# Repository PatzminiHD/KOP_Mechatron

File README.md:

# Mechatron

The git-repository for our KOP Project

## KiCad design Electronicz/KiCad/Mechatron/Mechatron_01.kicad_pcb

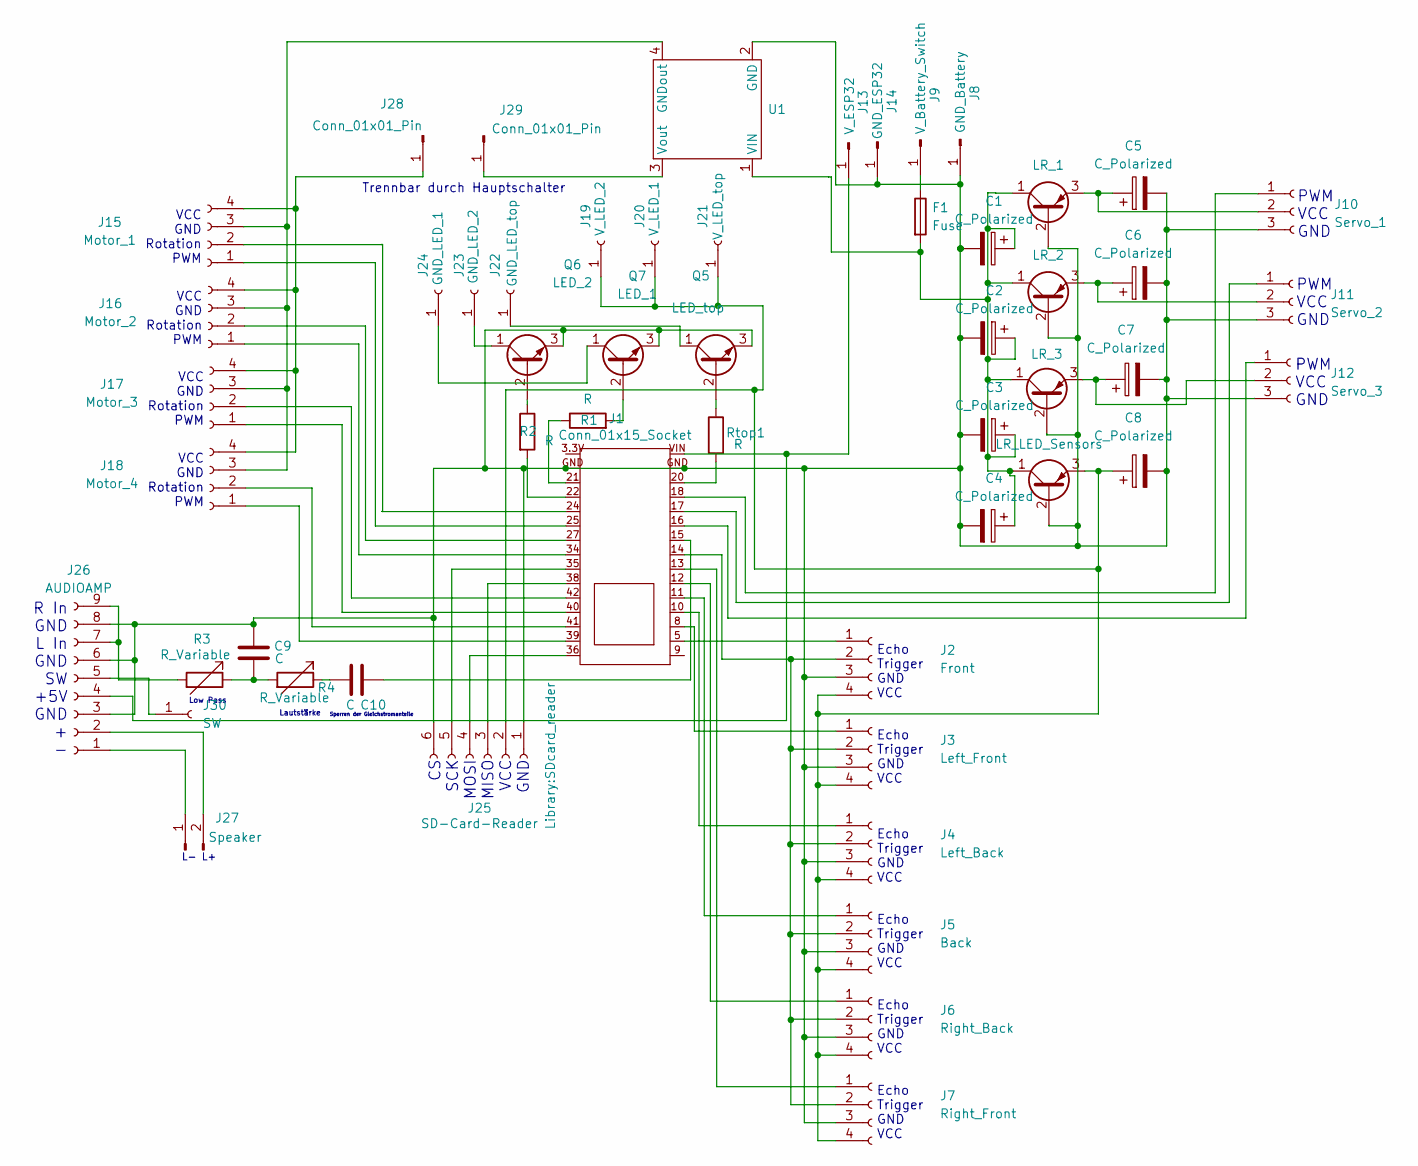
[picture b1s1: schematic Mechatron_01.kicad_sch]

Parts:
C1, C2, C3, C4, C5, C6, C7, C8: C_Polarized; C_Disc_D4.3mm_W1.9mm_P5.00mm
C9, C10: C; C_Disc_D3.0mm_W1.6mm_P2.50mm
F1: Fuse; Fuseholder_Clip-5x20mm_Eaton_1A5601-01_Inline_P20.80x6.76mm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
J1: Conn_01x15_Socket; ESP32
J2: Front; PinSocket_1x04_P2.54mm_Vertical
J3: Left_Front; PinSocket_1x04_P2.54mm_Vertical
J4: Left_Back; PinSocket_1x04_P2.54mm_Vertical
J5: Back; PinSocket_1x04_P2.54mm_Vertical
J6: Right_Back; PinSocket_1x04_P2.54mm_Vertical
J7: Right_Front; PinSocket_1x04_P2.54mm_Vertical
J8: GND_Battery; PinHeader_1x01_P2.54mm_Vertical
J9: V_Battery_Switch; PinHeader_1x01_P2.54mm_Vertical
J10: Servo_1; PinSocket_1x03_P2.54mm_Vertical
J11: Servo_2; PinSocket_1x03_P2.54mm_Vertical
J12: Servo_3; PinSocket_1x03_P2.54mm_Vertical
J13: V_ESP32; PinHeader_1x01_P2.54mm_Vertical
J14: GND_ESP32; PinHeader_1x01_P2.54mm_Vertical
J15: Motor_1; PinSocket_1x04_P2.54mm_Vertical
J16: Motor_2; PinSocket_1x04_P2.54mm_Vertical
J17: Motor_3; PinSocket_1x04_P2.54mm_Vertical
J18: Motor_4; PinSocket_1x04_P2.54mm_Vertical
J19: V_LED_2; PinSocket_1x01_P2.54mm_Vertical
J20: V_LED_1; PinSocket_1x01_P2.54mm_Vertical
J21: V_LED_top; PinSocket_1x01_P2.54mm_Vertical
J22: GND_LED_top; PinSocket_1x01_P2.54mm_Vertical
J23: GND_LED_2; PinSocket_1x01_P2.54mm_Vertical
J24: GND_LED_1; PinSocket_1x01_P2.54mm_Vertical
J25: SD-Card-Reader; SDcard_reader
J26: AUDIOAMP; PinSocket_1x09_P2.00mm_Vertical
J27: Speaker; PinHeader_1x02_P2.54mm_Vertical
J28, J29: Conn_01x01_Pin; PinHeader_1x01_P2.54mm_Vertical
J30: SW; PinSocket_1x01_P2.00mm_Vertical
Q1: LR_LED_Sensors; TO-126-3_Vertical
Q2: LR_3; TO-126-3_Vertical
Q3: LR_2; TO-126-3_Vertical
Q4: LR_1; TO-126-3_Vertical
Q5: LED_top; TO-92_Inline
Q6: LED_2; TO-92_Inline
Q7: LED_1; TO-92_Inline
R1, R2: R; R_Axial_DIN0207_L6.3mm_D2.5mm_P10.16mm_Horizontal
R3: R_Variable; Potentiometer_Bourns_3386C_Horizontal
R4: R_Variable; R_Axial_DIN0207_L6.3mm_D2.5mm_P10.16mm_Horizontal
Rtop1: R; R_Axial_DIN0207_L6.3mm_D2.5mm_P10.16mm_Horizontal
U1: Spannungsregler

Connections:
unnamed: C9.2, R3.1, R4.2
unnamed: C10.1, J1.15
unnamed: C10.2, R4.1
unnamed: J1.20, Rtop1.2
unnamed: J1.21, R1.1
unnamed: J1.22, R2.2
unnamed: J1.5, J2.1
unnamed: J1.14, J2.2, J3.2, J4.2, J5.2, J6.2, J7.2
unnamed: J1.8, J3.1
unnamed: J1.10, J4.1
unnamed: J1.11, J5.1
unnamed: J1.12, J6.1
unnamed: J1.13, J7.1
unnamed: F1.1, J9.1
unnamed: J1.18, J10.1
unnamed: C5.1, J10.2, Q4.3 (E)
unnamed: C1.2, C2.2, C3.2, C4.2, C5.2, C6.2, C7.2, C8.2, C9.1, J1.GND, J2.3, J3.3, J4.3, J5.3, J6.3, J7.3, J8.1, J10.3, J11.3, J12.3, J14.1, J25.1, J25.6, J26.3, J26.6, J26.8, Q1.2 (B), Q2.2 (B), Q3.2 (B), Q4.2 (B), Q5.3 (E), Q6.3 (E), Q7.3 (E), U1.2 (GND)
unnamed: J1.17, J11.1
unnamed: C6.1, J11.2, Q3.3 (E)
unnamed: J1.16, J12.1
unnamed: C7.1, J12.2, Q2.3 (E)
unnamed: J1.VIN, J13.1, J26.4
unnamed: J1.25, J15.1
unnamed: J1.24, J15.2
unnamed: J15.3, J16.3, J17.3, J18.3, U1.4 (GNDout)
unnamed: J15.4, J16.4, J17.4, J18.4, J28.1
unnamed: J1.34, J16.1
unnamed: J1.27, J16.2
unnamed: J1.40, J17.1
unnamed: J1.42, J17.2
unnamed: J1.39, J18.1
unnamed: J1.41, J18.2
unnamed: C8.1, J2.4, J3.4, J4.4, J5.4, J6.4, J7.4, J19.1, J20.1, J21.1, J25.2, Q1.3 (E)
unnamed: J22.1, Q5.1 (C)
unnamed: J23.1, Q6.1 (C)
unnamed: J24.1, Q7.1 (C)
unnamed: J1.38, J25.3
unnamed: J1.36, J25.4
unnamed: J1.35, J25.5
unnamed: J26.1, J27.1
unnamed: J26.2, J27.2
unnamed: J26.5, J30.1
unnamed: J26.7, J26.9, R3.2
unnamed: J29.1, U1.3 (Vout)
unnamed: C1.1, C2.1, C3.1, C4.1, F1.2, Q1.1 (C), Q2.1 (C), Q3.1 (C), Q4.1 (C), U1.1 (VIN)
unnamed: Q5.2 (B), Rtop1.1
unnamed: Q6.2 (B), R2.1
unnamed: Q7.2 (B), R1.2

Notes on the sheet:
Trennbar durch Hauptschalter
Echo Trigger GND VCC
PWM VCC GND
Low Pass
Lautstärke
VCC GND Rotation PWM
CS SCK MOSI MISO VCC GND
Sperren der Gleichstromanteile
R In GND L In GND SW +5V GND + -
L- L+

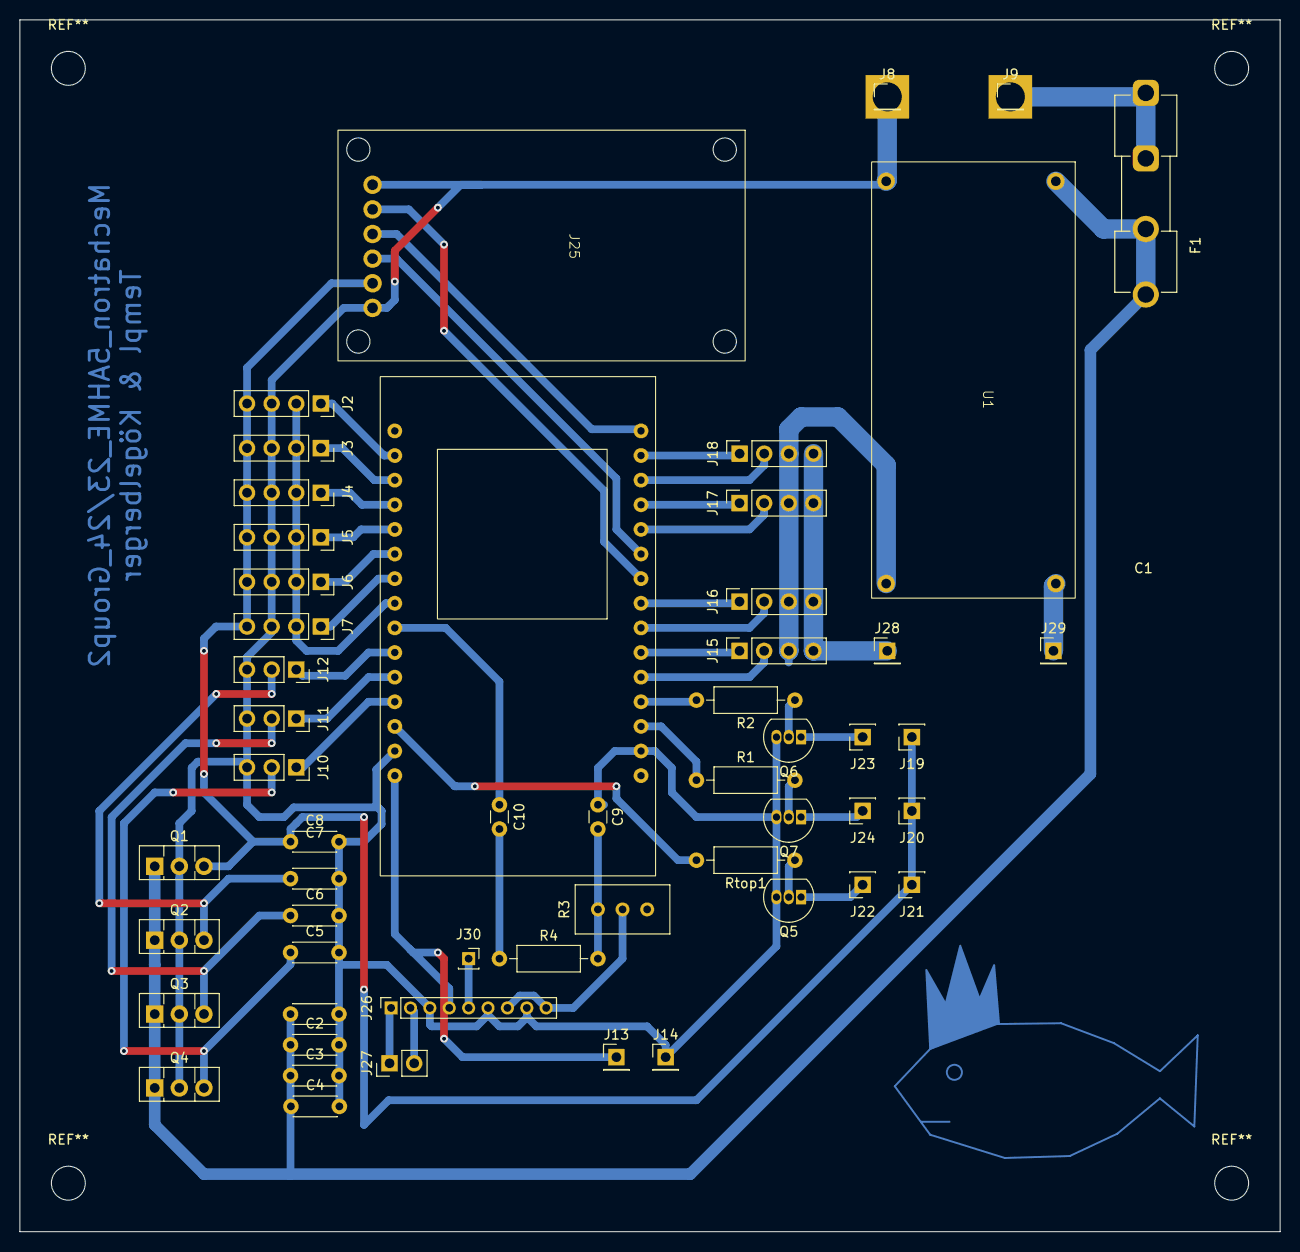
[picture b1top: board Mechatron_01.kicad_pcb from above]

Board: 2 copper layers, 130.0 x 125.0 mm, 54 parts (0 on the bottom side), 48 nets.

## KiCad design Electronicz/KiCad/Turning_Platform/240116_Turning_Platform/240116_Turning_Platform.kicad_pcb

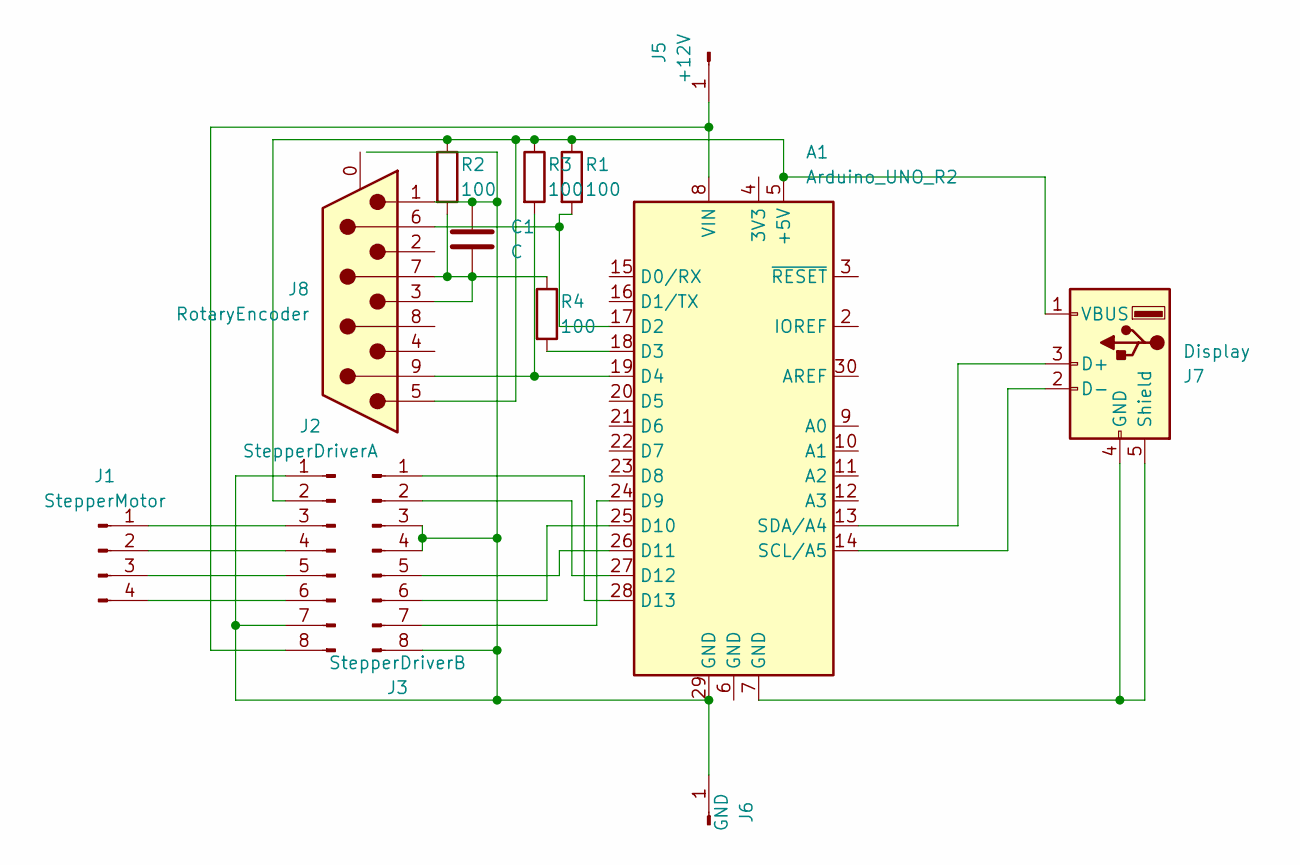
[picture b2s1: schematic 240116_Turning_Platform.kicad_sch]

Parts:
A1: Arduino_UNO_R2
C1: C; CP_Radial_D10.0mm_P7.50mm
J1: StepperMotor; PinHeader_1x04_P2.54mm_Vertical
J2: StepperDriverA; PinHeader_1x08_P2.54mm_Vertical
J3: StepperDriverB; PinHeader_1x08_P2.54mm_Vertical
J5: +12V; PinHeader_1x01_P2.54mm_Vertical
J6: GND; PinHeader_1x01_P2.54mm_Vertical
J7: Display; USB_A_CONNFLY_DS1095-WNR0
J8: RotaryEncoder; DSUB-9_Female_Horizontal_P2.77x2.84mm_EdgePinOffset7.70mm_H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
R1, R2, R3, R4: 100; R_Axial_DIN0207_L6.3mm_D2.5mm_P10.16mm_Horizontal

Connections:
unnamed: A1.5 (+5V), J2.2, J7.1 (VBUS), J8.5, R1.1, R2.1, R3.1
unnamed: A1.17 (D2), J8.6, R1.2
unnamed: A1.18 (D3), R4.2
unnamed: A1.19 (D4), J8.9, R3.2
unnamed: A1.24 (D9), J3.7
unnamed: A1.25 (D10), J3.6
unnamed: A1.26 (D11), J3.5
unnamed: A1.27 (D12), J3.2
unnamed: A1.28 (D13), J3.1
unnamed: A1.14 (SCL/A5), J7.2 (D-)
unnamed: A1.13 (SDA/A4), J7.3 (D+)
unnamed: A1.8 (VIN), J2.8, J5.1
unnamed: C1.2, J8.3, J8.7, R2.2, R4.1
unnamed: J1.1, J2.3
unnamed: J1.2, J2.4
unnamed: J1.3, J2.5
unnamed: J1.4, J2.6
unnamed: A1.29 (GND), C1.1, J2.1, J2.7, J3.3, J3.4, J3.8, J6.1, J8.1
unnamed: A1.7 (GND), J7.4 (GND), J7.5 (Shield)

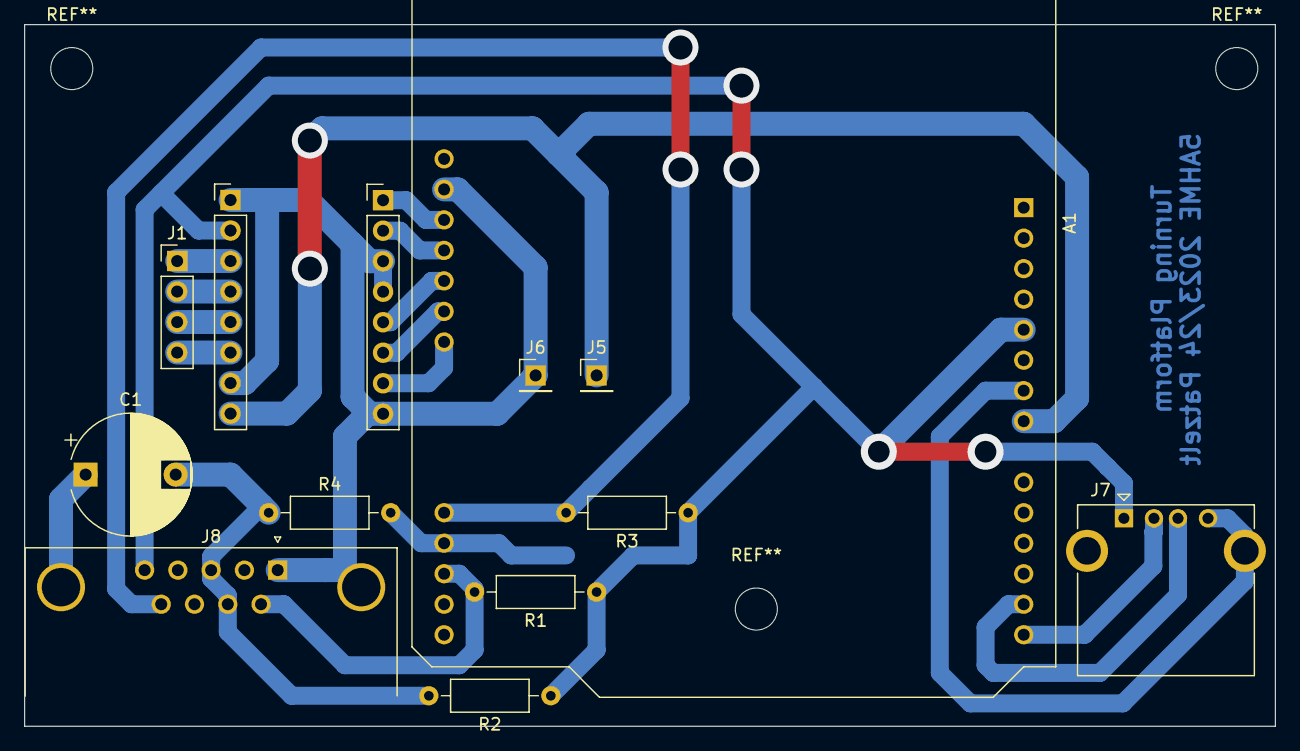
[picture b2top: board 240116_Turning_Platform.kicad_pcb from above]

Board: 2 copper layers, 104.1 x 58.4 mm, 13 parts (0 on the bottom side), 19 nets.

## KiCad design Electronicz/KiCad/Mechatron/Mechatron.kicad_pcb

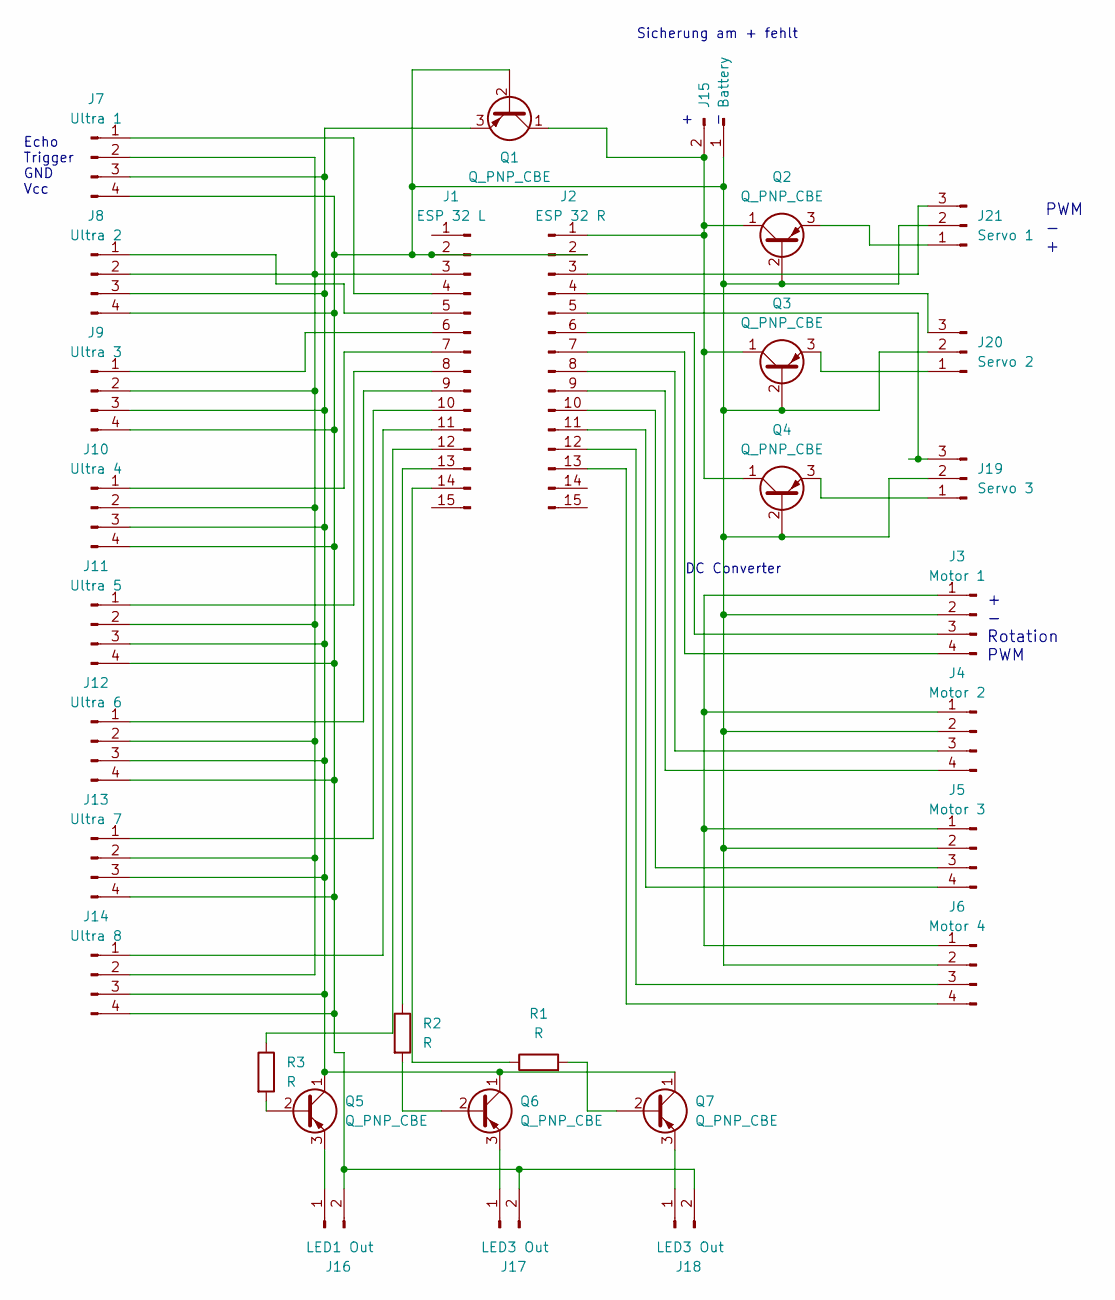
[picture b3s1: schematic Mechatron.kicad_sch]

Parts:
J1: ESP 32 L; PinHeader_1x15_P2.54mm_Vertical
J2: ESP 32 R; PinHeader_1x15_P2.54mm_Vertical
J3: Motor 1; PinHeader_1x04_P2.54mm_Vertical
J4: Motor 2; PinHeader_1x04_P2.54mm_Vertical
J5: Motor 3; PinHeader_1x04_P2.54mm_Vertical
J6: Motor 4; PinHeader_1x04_P2.54mm_Vertical
J7: Ultra 1; PinHeader_1x04_P2.54mm_Vertical
J8: Ultra 2; PinHeader_1x04_P2.54mm_Vertical
J9: Ultra 3; PinHeader_1x04_P2.54mm_Vertical
J10: Ultra 4; PinHeader_1x04_P2.54mm_Vertical
J11: Ultra 5; PinHeader_1x04_P2.54mm_Vertical
J12: Ultra 6; PinHeader_1x04_P2.54mm_Vertical
J13: Ultra 7; PinHeader_1x04_P2.54mm_Vertical
J14: Ultra 8; PinHeader_1x04_P2.54mm_Vertical
J15: Battery; SolderWire-0.5sqmm_1x02_P4.6mm_D0.9mm_OD2.1mm
J16: LED1 Out; PinHeader_1x02_P2.54mm_Vertical
J17, J18: LED3 Out; PinHeader_1x02_P2.54mm_Vertical
J19: Servo 3; PinHeader_1x03_P2.54mm_Vertical
J20: Servo 2; PinHeader_1x03_P2.54mm_Vertical
J21: Servo 1; PinHeader_1x03_P2.54mm_Vertical
Q1, Q2, Q3, Q4, Q5, Q6, Q7: Q_PNP_CBE; PinHeader_1x03_P2.54mm_Vertical
R1, R2, R3: R; R_Axial_DIN0207_L6.3mm_D2.5mm_P10.16mm_Horizontal

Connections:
unnamed: J1.2, J2.2, J3.2, J4.2, J5.2, J6.2, J7.4, J8.4, J9.4, J10.4, J11.4, J12.4, J13.4, J14.4, J15.1, J16.2, J17.2, J18.2, J19.2, J20.2, J21.2, Q1.2 (B), Q2.2 (B), Q3.2 (B), Q4.2 (B)
unnamed: J1.3, J7.2, J8.2, J9.2, J10.2, J11.2, J12.2, J13.2, J14.2
unnamed: J1.4, J7.1
unnamed: J1.5, J8.1
unnamed: J1.6, J9.1
unnamed: J1.7, J10.1
unnamed: J1.8, J11.1
unnamed: J1.9, J12.1
unnamed: J1.10, J13.1
unnamed: J1.11, J14.1
unnamed: J1.12, R3.1
unnamed: J1.13, R2.1
unnamed: J1.14, R1.1
unnamed: J2.3, J21.3
unnamed: J2.4, J20.3
unnamed: J2.6, J3.3
unnamed: J2.7, J3.4
unnamed: J2.8, J4.3
unnamed: J2.9, J4.4
unnamed: J2.10, J5.3
unnamed: J2.11, J5.4
unnamed: J2.12, J6.3
unnamed: J2.13, J6.4
unnamed: J3.1, J4.1, J5.1, J6.1
unnamed: J7.3, J8.3, J9.3, J10.3, J11.3, J12.3, J13.3, J14.3, Q1.3 (E), Q5.1 (C), Q6.1 (C), Q7.1 (C)
unnamed: J2.1, J15.2, Q1.1 (C), Q2.1 (C), Q3.1 (C), Q4.1 (C)
unnamed: J16.1, Q5.3 (E)
unnamed: J17.1, Q6.3 (E)
unnamed: J18.1, Q7.3 (E)
unnamed: J19.1, Q4.3 (E)
unnamed: J2.5, J19.3
unnamed: J20.1, Q3.3 (E)
unnamed: J21.1, Q2.3 (E)
unnamed: Q5.2 (B), R3.2
unnamed: Q6.2 (B), R2.2
unnamed: Q7.2 (B), R1.2

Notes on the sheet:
+ - Rotation PWM
DC Converter
Echo Trigger GND Vcc
PWM - +
Sicherung am + fehlt
+ -

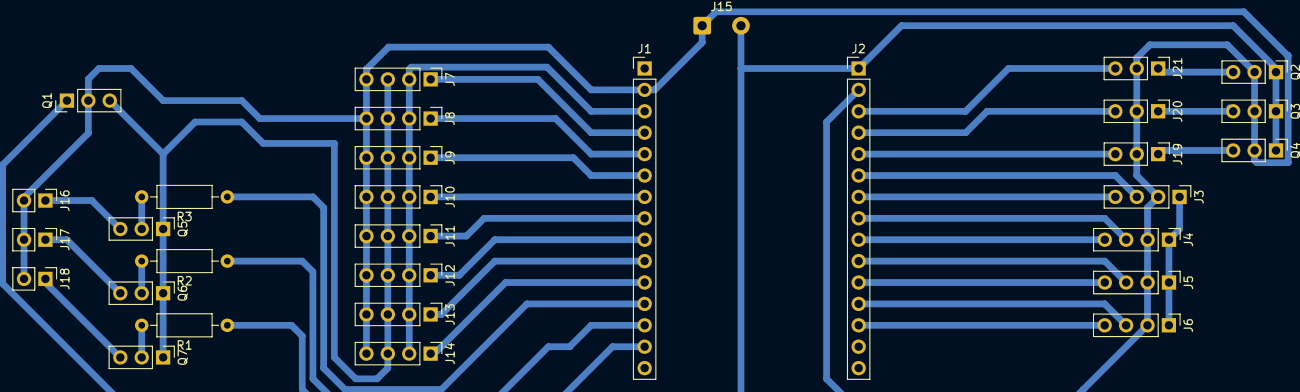
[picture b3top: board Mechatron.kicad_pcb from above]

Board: 2 copper layers, 31 parts (0 on the bottom side), 36 nets.

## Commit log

2023-09-21 Testcommit
2023-09-21 Update Readme, delete test commit
2023-09-21 Initial commit of ESP32 Codebase
2023-09-25 Add v0.1.0 of Firmware
2023-09-26 adding folders / creating files
2023-09-26 list electronicz
2023-09-27 Add Method to move in any given Direction
2023-09-28 Add links; rename directory
2023-10-03 add KiCad folder
2023-10-06 create Schematic and Footprints
2023-10-06 Add Program Flowchart
2023-10-07 update schematic and create PCB
2023-10-08 fix esp 32 pin distance
2023-10-08 change placement on the pcb
2023-10-08 Add KiCad ESP Symbol and Footprint
2023-10-10 update schematic
2023-10-10 Implement Controller Connection
2023-10-17 Add ability to play songs and change MovementMode
2023-10-24 Fix movement selection
2023-10-24 Add Audio output Library
2023-10-24 Add mp3 player
2023-10-24 update old schematic
2023-10-24 Add led class
2023-10-24 Add new schematic
2023-10-26 KiCad Footprint zuweisen
2023-10-26 Implement Audio playback from SD-Card. Fix #4
2023-10-26 Fix renaming of mp3.h to MP3.h
2023-10-27 add amplifier and speaker pins
2023-10-29 add TODO
2023-11-05 add filter and label of the Pin Header
2023-11-07 Add Bodenplatte
2023-11-07 Add Datasheets
2023-11-07 Measure Ultrasonic Sonic Sensor Distance
2023-11-07 Platinendesign
2023-11-14 Add Führerhaus and Aufbau
2023-11-14 Add USS Pins
2023-11-14 Move Files back to Electronicz directory
2023-11-14 pcb design
2023-11-14 adding sdcard-reader
2023-11-14 Add Mittelteil
2023-11-14 Create PCB
2023-11-21 Add Video Assets
2023-11-21 Add Code for Ultrasonic Sensors
2023-11-21 Finishing PCB
2023-11-21 Add Halterung
2023-11-23 add concept of platform
2023-11-25 Add Stepper Motor
2023-11-25 Improve Stepper Motor Model
2023-11-25 Add mounting Holes
2023-11-25 Add Large Bearing
2023-11-25 ähhmmm rotating platform
2023-11-25 Add Stand
2023-11-26 Add Code for turning Platform
2023-11-27 Add Test object for Stepper Connection
2023-11-28 Add Printsettings
2023-11-28 add stand stl file
2023-11-28 Add Bodenplatte PDF
    with main measurements
2023-11-28 add platform flange stl file
2023-11-28 Add Motorhalterung front + rear
2023-11-28 Parts refreshed
2023-11-28 create video script
2023-11-28 Add details Führerhaus & Mittelteil
2023-11-28 Edit Bodenplatte, Führerhaus, Mittelteil
    Abstand zwischen Räder vergrößert, Vorderachse weiter nach vorne verschoben, Mittelteil länge verkleinert
2023-11-29 Work on turning platform code
2023-12-05 Add Hinterteil
2023-12-05 editing bottom plate and chassis
2023-12-05 making LED-holders
2023-12-06 remaking bottom plate and fixing of the assembly
2023-12-12 add stl file
2023-12-12 add new stl file
2023-12-12 add new led holder stl file
2023-12-12 add new stl file for led holder
2023-12-12 Changes hinterteil
2023-12-12 Edited CAD Files
2023-12-16 Add details mittelteil
2023-12-19 Add Rollos & Blaulicht oben
2023-12-19 Add Details
2023-12-19 update videoscript
2023-12-19 add Mr. Fich
2023-12-19 Add Details Rundungen Mittelteil
2023-12-22 Add Model of 360° Servo
2023-12-23 kleine Änderungen
2023-12-23 Upload test program to test ultra sonic sensors
2023-12-23 andere kleine unwichtige Änderungen
2023-12-23 add Platine and more
2023-12-24 add battery
2023-12-25 Add mental breakdown
2023-12-25 Add some more errors
2023-12-25 Add Türgriffe & Schraubhalterung Mittel- und Hinterteil
2023-12-25 Reduce width -30mm
2023-12-25 Add Rückspiegel Links und Rechts
2023-12-26 add battery to asm
2023-12-26 update details
2023-12-26 Add Detail Türrahmen
2023-12-27 changing videoscript
2023-12-28 Add Ein/Aus-Schalter
2023-12-29 Add Schalter to Aufbau.asm & Bodenplatte
2023-12-29 Minor resize of motors
2023-12-29 Add chamfer to hinter- & mittelteil bottom
2023-12-29 Add Koks&KögsKG Intro
2023-12-29 Add V01 of Halterung-Stufen + details Führerhaus
2024-01-03 Fehler
2024-01-09 edited motor mount + base plate
2024-01-09 add speaker model
2024-01-16 fixed baseplate & motor mount
2024-01-16 fixed baseplate mounting holes
2024-01-16 Clear old github files
2024-01-16 Fix Motorhalterung
2024-01-16 Add Trail Files
2024-01-16 fixed baseplate 3.0
2024-01-16 Start on turning platform pcb
2024-01-16 Add Rotary Encoder support
2024-01-16 Make Turning Plate PCB
2024-01-19 Add Endlagenschalter
2024-01-19 Finish Endlagenschalter
2024-01-19 Update Endlagenschalter
2024-01-19 Add Case for rotary encoder
2024-01-20 Add Rotary Encoder Top Attachment
2024-01-20 Export Models that are ready to print
2024-01-20 Update Stepper Pins for PCB
2024-01-21 add windshield and windows
2024-01-21 fix holes
2024-01-21 Add Battery Holder
2024-01-21 Fine-tune size of Rotary Encoder Top
2024-01-21 Add Speaker Mount
2024-01-22 add powerbank model
2024-01-22 random shit
2024-01-22 Update Video Script
2024-01-22 coloring and editing Front
2024-01-22 add ultrasonicsensor mount
2024-01-23 fix motormount
2024-01-23 Add the (hopefully) correct version of Bodenplatte
2024-01-23 Add Zapfen to Hinterteil
2024-01-23 Add Creo whitescreen of death
2024-01-23 Add hole for cable
2024-01-23 Refit holes for ultraholder on bodenplatte
2024-01-23 Re-place hole for main-switch on bodenplatte
2024-01-23 Add holes for zapfen from hinterteil in bodenplatte
2024-01-23 Add Zapfen on mittelteil & löcher on Bodenplatte
2024-01-23 Add Zapfen on Führerhaus & Löcher on Grundplatte
2024-01-23 latest aufbau version
2024-01-24 change baseplate
2024-01-24 Add code for LEDs
2024-01-24 Update Pin numbers
2024-01-24 Add Servo Code
2024-01-24 Update Turning Platform PCB
2024-01-24 add bearing and shaft holder
2024-01-24 add stl files
2024-01-24 update aufbau
2024-01-25 Export step files
2024-01-25 Update Ultraholder stl file
2024-01-25 add abstandshalter stl file
2024-01-25 Remove Square Hole from Ultraholder
2024-01-25 Remove KiCad lock files
2024-01-25 Implement Blinking blue LEDs
2024-01-27 Add turning while in MovementMode_JoyLeft; Turn off LEDs on startup
2024-01-27 Add CAD-News Intro Project
2024-01-27 Add Credits file
2024-01-30 Update Script and Credits
2024-01-30 change Schalter on Bodenplatte
2024-01-30 Fix motor
2024-01-30 fin_motormountfront & rear
2024-01-30 Make LEDs work
2024-01-30 rename motormount files
2024-01-30 rename motorhalterung
2024-01-30 Add drawings folder & ladder-shaft holder drawing
2024-01-30 fix motormounts and assemble motors
2024-01-30 Rename folder from "Moving_Platform" to "Turning_Platform"
2024-01-31 Add drawing of ladder shaft holder
2024-01-31 Add drawing of ladder bearing holder
2024-01-31 Fix UpdatingInt Function
2024-01-31 revise whole design
2024-02-01 Update Drawing
2024-02-02 Edits
2024-02-02 Update Stepper Motor Connections
2024-02-02 Update Stepper Connections Again because they are not the same on both StepperMotors
2024-02-02 Update Turning Platform Code
2024-02-03 add dxf and drawing files
2024-02-03 höhe der Platine veringern
2024-02-03 Remove PWM Control
2024-02-03 Add ServoController to Movement, Test Motor Signals
2024-02-03 Copy current status to subfolder for Credits animation
2024-02-03 Work on Credits Assembly
2024-02-04 Add new Creo Errors
2024-02-04 Add Drehleiter to Assembly
2024-02-05 Add drawing led holder
2024-02-05 add pic
2024-02-05 Add LED Holder ASM DRW
2024-02-05 Add Alles Fehlt
2024-02-06 add new stl files
2024-02-06 Add Low Voltage Detector Curcuit
2024-02-06 Add simple aufbau
2024-02-06 Remove Sensors that aren't needed anymore
2024-02-06 Add Servo Control
2024-02-06 Add Detection for Konami Code
2024-02-06 ultraholder front fix
2024-02-13 Plot Turning Platform PCB
2024-02-13 add rückspiegel stl files
2024-02-13 Add CAD-News Card
2024-02-13 add hinterteil stl
2024-02-17 Add Konami Code Detection
2024-02-17 Fix Servo Controls
2024-02-17 Fix MP3 Playing
2024-02-18 Make enclosure for Small Speaker
2024-02-18 Export Speaker Case
2024-02-19 Make Cable Protector
2024-02-19 Export Cable Protector
2024-02-22 Add Speaker Box to assembly
2024-02-22 Export führerhaus
2024-02-22 Add Creo Errors
2024-02-22 Add Cable Connectors; Fix Leiter Auflage
2024-02-22 Update Speaker box
2024-02-22 Put Servo, Aufsatz and Zahnrad in one assembly
2024-02-23 Update Video Script; Add Survey Results
2024-02-23 Record Theodore Voicelines
2024-02-23 Replace Existing Gears with Larger ones
2024-02-23 Add Gear Values
2024-02-24 Add Servo Halter unten
2024-02-24 Finish Program Flow Chart
2024-02-24 Fix Servo Halter unten; Remove old stl file
2024-02-26 Export Führerhaus and Mittelteil to .stl
2024-02-26 Increase size of rückspiegel rod
2024-02-26 Export Rückspiegel stl
2024-02-27 Update Servo Halter
2024-02-27 Export Servo Halter and Zahnräder
2024-02-27 remake servo_halter_unten
2024-03-04 export pcb and schematic pdfs
2024-03-05 Create Code Printouts
2024-03-05 Update Credits Assembly
2024-03-06 Finish Credits Assembly
2024-03-09 ahhhhhhhhhhhhhhhh
2024-03-10 Add Connector Diagram
2024-03-10 Add Timeout to Sensor Poll
2024-03-10 Make values private
2024-03-12 Remove Code related to Buzzer
2024-03-12 Improve init phase
2024-03-12 Add LICENSE
2024-03-19 Update battery holder
2024-03-19 Add Cable Holder for Motorhalterung
2024-03-19 Make led functions public
2024-03-19 Add Dancing and MP3 Playback
2024-03-19 Add LED Strip Pin
2024-03-28 Move Koks&Kögs KG Intro Object into Directory
2024-03-29 Remove .obj files from .gitignore
2024-03-29 Add Outro Assets
2024-03-31 Start on Presentation
2024-03-31 Finish Outro Animation
2024-04-01 Fix title of page
2024-04-01 Render Video
2024-04-01 Work on Outro Clip
2024-04-01 Add Outro Song to Credits
2024-04-06 Work on Video
2024-04-07 Finish CAD-News Segment
2024-04-08 Add subtitles to video
2024-04-08 Finish Video
